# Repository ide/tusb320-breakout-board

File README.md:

# TUSB320 Breakout Board

This PCB is a breakout board for the Texas Instruments TUSB320 chip and a USB-C connector (16+8 dummy pins).

## Features

- Headers for each pin of the TUSB320 chip and USB-C connector
- Built-in connections between the USB-C connector's CC1 and CC2 pins and the TUSB320 chip's respective CC1 and CC2 pins
- Pads for smoothing capacitors connected to voltage sources, namely VBUS and VDD. Smoothing capacitors are typically optional and you can leave them off (do not short to ground!) but filtering noise is a good practice.
- A pad for the 887K ohm resistor between the TUSB320 chip's VBUS_DET pin and the USB-C connector's VBUS pin. Note: VBUS_DET and VBUS are not connected by default.
- A jumper pad to connect VBUS_DET to VBUS with an 887K ohm resistor in between. You can either bridge the pads or use a 0 ohm resistor.

## Ordering

TBA

## BOM
| Reference | Part description                  | Size                                     | Example part #                                                                                                   |
|-----------|-----------------------------------|------------------------------------------|------------------------------------------------------------------------------------------------------------------|
| R1        | 887K ohm resistor                 | 0402                                     | [ERJ-2RKF8873X](https://www.digikey.com/en/products/detail/panasonic-electronic-components/ERJ-2RKF8873X/192503) |
| R2        | 0 ohm resistor (optional)         | 0402                                     | [ERJ-2GE0R00X](https://www.digikey.com/en/products/detail/panasonic-electronic-components/ERJ-2GE0R00X/146727)   |
| C1        | 1μF 35V capacitor                 | 0402                                     | [GRM155R6YA105KE11D](https://www.digikey.com/en/products/detail/murata-electronics/GRM155R6YA105KE11D/4905162)   |
| C2        | 0.1μF 5V capacitor                | 0402                                     | [04025C104KAT2A](https://www.digikey.com/en/products/detail/kyocera-avx/04025C104KAT2A/6564238)                  |
| J1        | USB-C connector (16+8 dummy pins) | Surface mount, right angle, through hole | [DX07S016JA1R1500](https://www.digikey.com/en/products/detail/jae-electronics/DX07S016JA1R1500/11585731)         |
| J2, J3    | 1x9 male through hole headers     |                                          | [PRPC009SAAN-RC](https://www.digikey.com/en/products/detail/sullins-connector-solutions/PRPC009SAAN-RC/2775245)  |
| U1        | TUSB320, TUSB320LI, TUSB320LAI    | 12-X2QFN                                 | [TUSB320LAIRWBR](https://www.digikey.com/en/products/detail/texas-instruments/TUSB320LAIRWBR/5722618)            |

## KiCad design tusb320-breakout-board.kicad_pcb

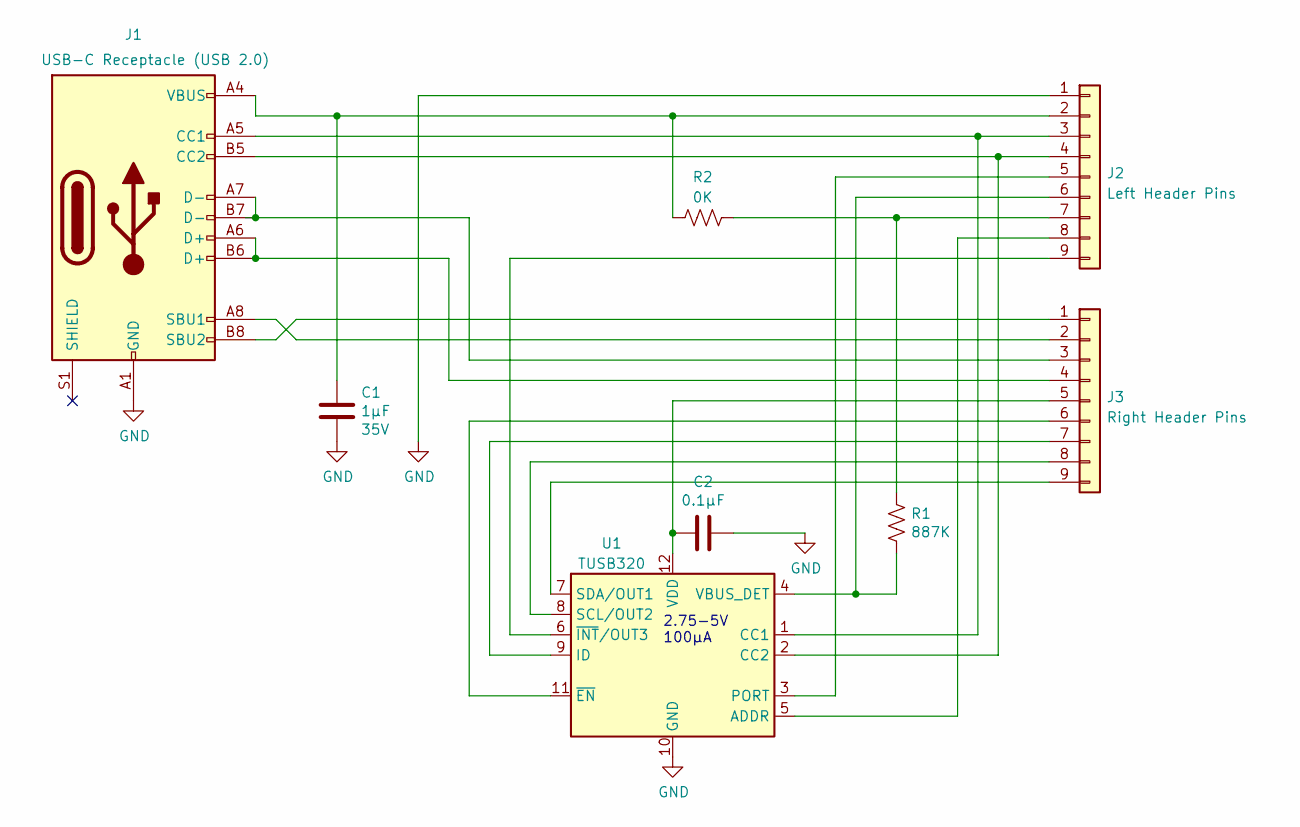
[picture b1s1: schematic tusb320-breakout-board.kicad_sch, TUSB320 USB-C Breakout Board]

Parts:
C1: 1μF; C_0402_1005Metric; Voltage 35V
C2: 0.1μF; C_0402_1005Metric
J1: USB-C Receptacle (USB 2.0); USB_C_Receptacle_JAE_DX07S016JA1R1500
J2: Left Header Pins; PinHeader_1x09_P2.54mm_Vertical
J3: Right Header Pins; PinHeader_1x09_P2.54mm_Vertical
R1: 887K; R_0402_1005Metric
R2: 0K; R_0402_1005Metric
U1: TUSB320; Texas_X2QFN-12_1.6x1.6mm_P0.4mm

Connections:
GND: C1.1, C2.1, J1.A1 (GND), J1.A12 (GND), J1.B1 (GND), J1.B12 (GND), J2.1, U1.10 (GND)
unnamed: C1.2, J1.A4 (VBUS), J1.A9 (VBUS), J1.B4 (VBUS), J1.B9 (VBUS), J2.2, R2.1
unnamed: C2.2, J3.5, U1.12 (VDD)
unnamed: J1.A5 (CC1), J2.3, U1.1 (CC1)
unnamed: J1.A6 (D+), J1.B6 (D+), J3.4
unnamed: J1.A7 (D-), J1.B7 (D-), J3.3
unnamed: J1.A8 (SBU1), J3.2
unnamed: J1.B5 (CC2), J2.4, U1.2 (CC2)
unnamed: J1.B8 (SBU2), J3.1
unnamed: J2.5, U1.3 (PORT)
unnamed: J2.6, R1.2, U1.4 (VBUS_DET)
unnamed: J2.7, R1.1, R2.2
unnamed: J2.8, U1.5 (ADDR)
unnamed: J2.9, U1.6 (~INT/OUT3)
unnamed: J3.6, U1.11 (~EN)
unnamed: J3.7, U1.9 (ID)
unnamed: J3.8, U1.8 (SCL/OUT2)
unnamed: J3.9, U1.7 (SDA/OUT1)

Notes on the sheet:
2.75-5V 100μA

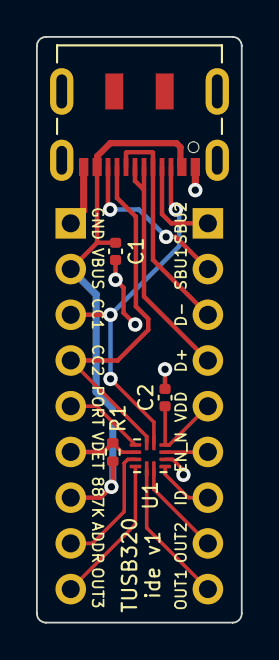
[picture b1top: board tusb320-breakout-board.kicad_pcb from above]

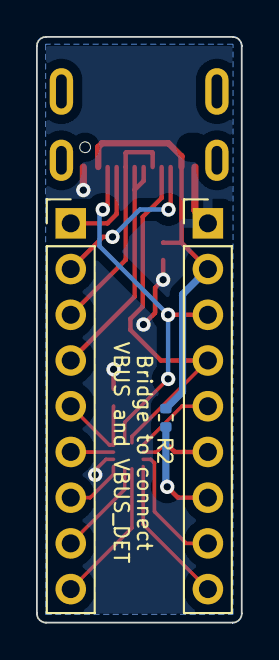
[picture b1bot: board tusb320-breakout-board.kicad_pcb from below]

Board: 2 copper layers, 11.4 x 32.5 mm, 8 parts (3 on the bottom side), 18 nets.

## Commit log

2022-09-19 Add v1 draft of PCB
2022-09-19 Add plotted Gerbers
2022-09-19 Add jumper to connect VBUS to VBUS_DET
2022-09-19 Add MIT License
2022-09-24 [readme] Add board preview
